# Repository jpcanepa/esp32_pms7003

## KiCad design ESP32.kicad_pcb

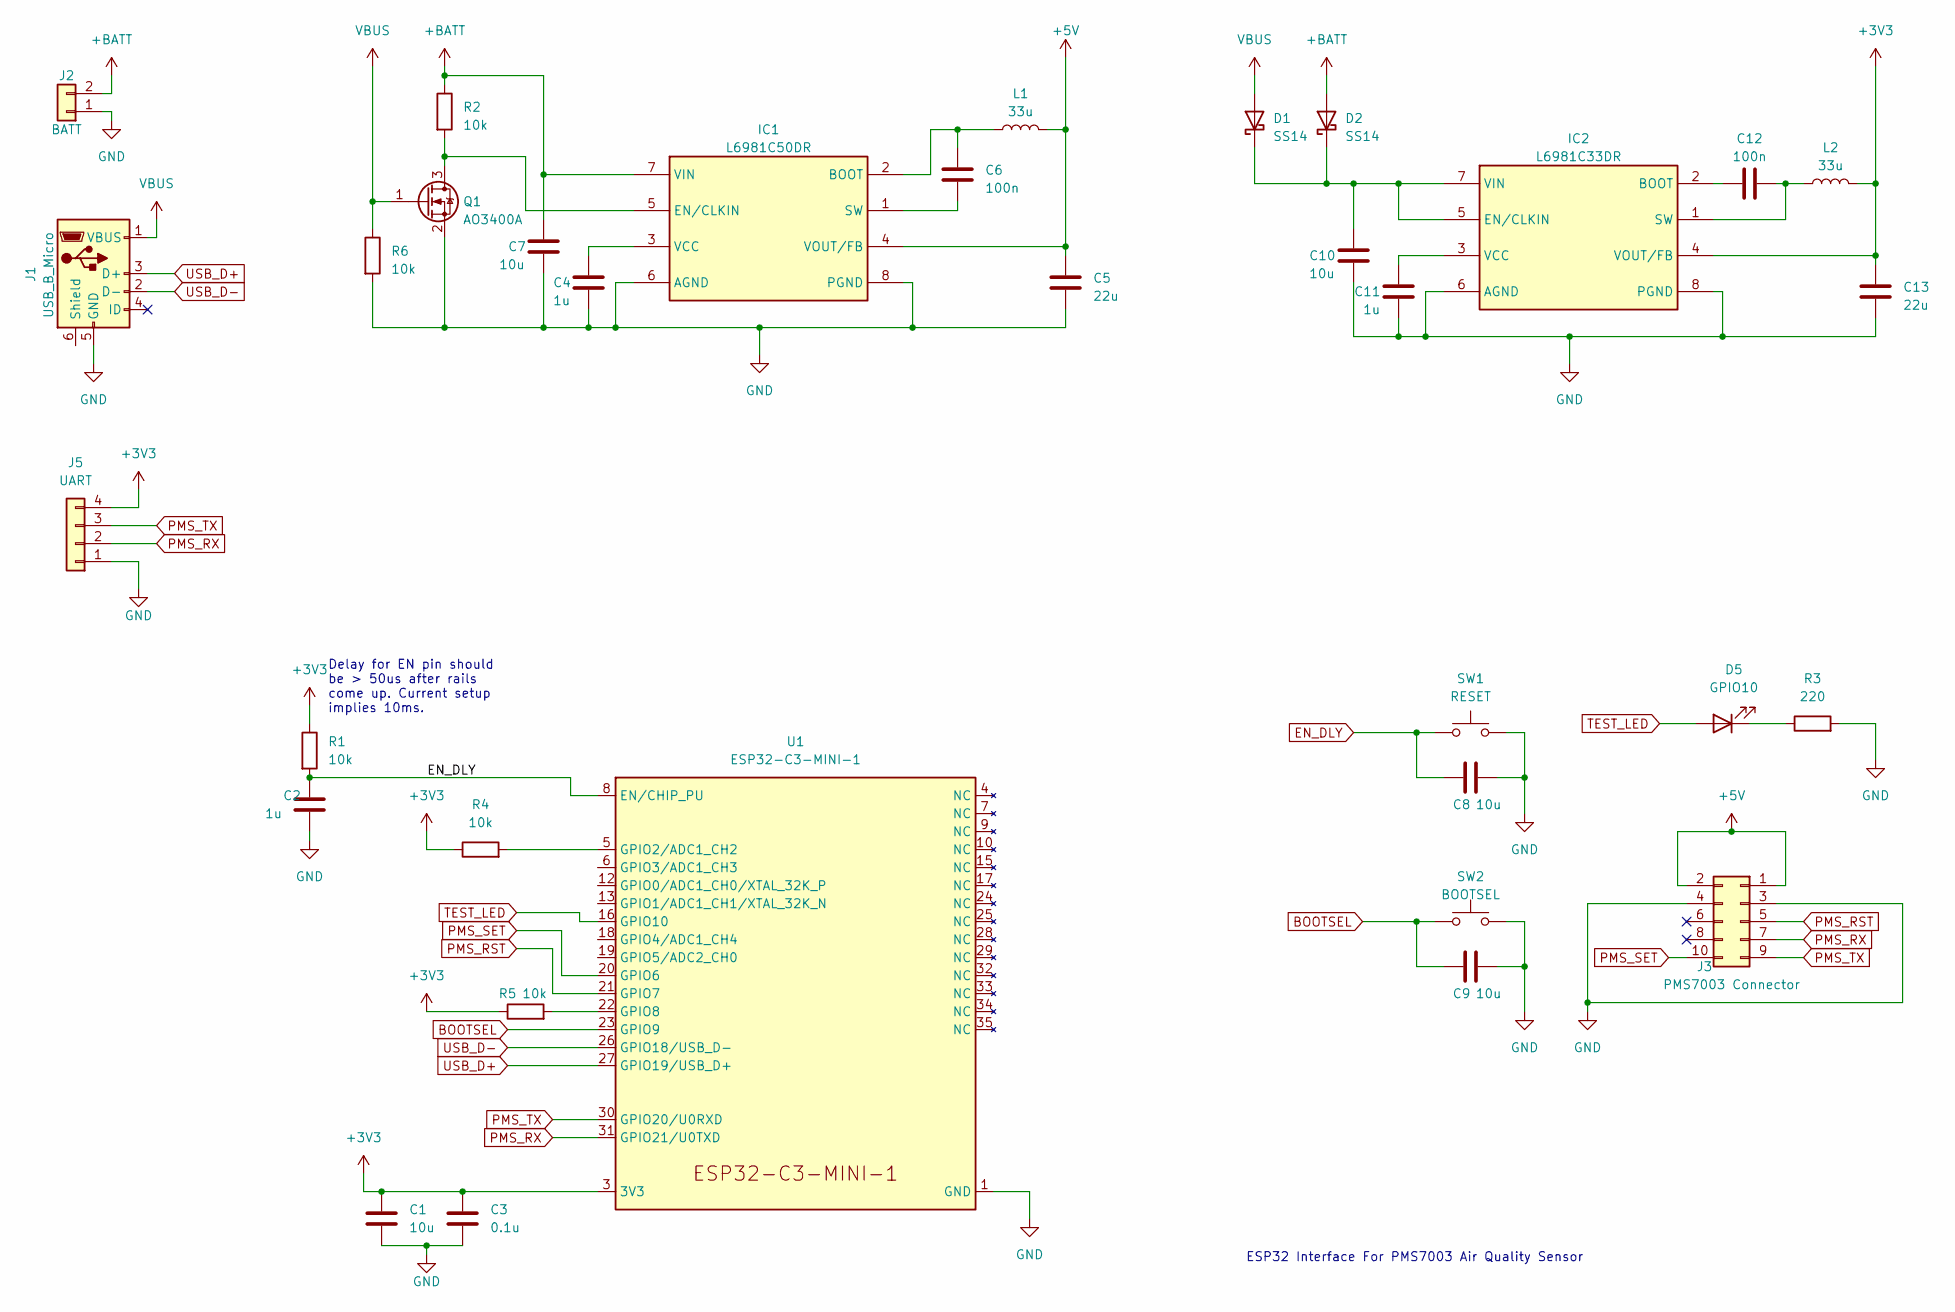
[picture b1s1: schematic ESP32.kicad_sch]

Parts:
C1, C7, C8, C9, C10: 10u; C_0603_1608Metric_Pad1.08x0.95mm_HandSolder
C2, C4, C11: 1u; C_0603_1608Metric_Pad1.08x0.95mm_HandSolder
C3: 0.1u; C_0603_1608Metric_Pad1.08x0.95mm_HandSolder
C5, C13: 22u; C_0603_1608Metric_Pad1.08x0.95mm_HandSolder
C6, C12: 100n; C_0603_1608Metric_Pad1.08x0.95mm_HandSolder
D1, D2: SS14; D_SMA_Handsoldering
D5: GPIO10; LED_0603_1608Metric_Pad1.05x0.95mm_HandSolder
IC1: L6981C50DR; SOIC127P600X175-8N; Mouser Part Number 511-L6981C50DR
IC2: L6981C33DR; SOIC127P600X175-8N; Mouser Part Number 511-L6981C50DR
J1: USB_B_Micro; USB_Mini-B_Wuerth_65100516121_Horizontal
J2: BATT; PinHeader_1x02_P2.54mm_Vertical_SMD_Pin1Right
J3: PMS7003 Connector; PinSocket_2x05_P1.27mm_Vertical_SMD
J5: UART; PinHeader_1x04_P2.54mm_Vertical_SMD_Pin1Right
L1, L2: 33u; L_Murata_29xxxC
Q1: AO3400A; SOT-23
R1, R2, R4, R5, R6: 10k; R_0603_1608Metric_Pad0.98x0.95mm_HandSolder
R3: 220; R_0603_1608Metric_Pad0.98x0.95mm_HandSolder
SW1: RESET; SW_Push_1P1T_NO_Vertical_Wuerth_434133025816
SW2: BOOTSEL; SW_Push_1P1T_NO_Vertical_Wuerth_434133025816
U1: ESP32-C3-MINI-1

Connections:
+3V3: C1.1, C3.1, C13.1, IC2.4 (VOUT/FB), J5.4, L2.2, R1.1, R4.1, R5.1, U1.3 (3V3)
+5V: C5.1, IC1.4 (VOUT/FB), J3.1, J3.2, L1.2
+BATT: C7.1, D2.2 (A), IC1.7 (VIN), J2.2, R2.1
BOOTSEL: C9.1, SW2.1, U1.23 (GPIO9)
EN_DLY: C2.1, C8.1, R1.2, SW1.1, U1.8 (EN/CHIP_PU)
GND: C1.2, C2.2, C3.2, C4.2, C5.2, C7.2, C8.2, C9.2, C10.2, C11.2, C13.2, IC1.6 (AGND), IC1.8 (PGND), IC2.6 (AGND), IC2.8 (PGND), J1.5 (GND), J2.1, J3.3, J3.4, J5.1, Q1.2 (S), R3.2, R6.2, SW1.2, SW2.2, U1.1 (GND), U1.2 (GND), U1.36 (GND), U1.37 (GND), U1.38 (GND), U1.39 (GND), U1.40 (GND), U1.41 (GND), U1.42 (GND), U1.43 (GND), U1.44 (GND), U1.45 (GND), U1.46 (GND), U1.47 (GND), U1.48 (GND), U1.49 (GND), U1.50 (GND), U1.51 (GND), U1.52 (GND), U1.53 (GND)
unnamed: C10.1, D1.1 (K), D2.1 (K), IC2.5 (EN/CLKIN), IC2.7 (VIN)
unnamed: D5.1 (K), R3.1
unnamed: C6.2, IC1.2 (BOOT), L1.1
unnamed: IC1.5 (EN/CLKIN), Q1.3 (D), R2.2
unnamed: C6.1, IC1.1 (SW)
unnamed: C4.1, IC1.3 (VCC)
unnamed: C12.1, IC2.2 (BOOT)
unnamed: C12.2, IC2.1 (SW), L2.1
unnamed: C11.1, IC2.3 (VCC)
unnamed: R4.2, U1.5 (GPIO2/ADC1_CH2)
unnamed: R5.2, U1.22 (GPIO8)
PMS_RST: J3.5, U1.21 (GPIO7)
PMS_RX: J3.7, J5.2, U1.31 (GPIO21/U0TXD)
PMS_SET: J3.10, U1.20 (GPIO6)
PMS_TX: J3.9, J5.3, U1.30 (GPIO20/U0RXD)
TEST_LED: D5.2 (A), U1.16 (GPIO10)
USB_D+: J1.3 (D+), U1.27 (GPIO19/USB_D+)
USB_D-: J1.2 (D-), U1.26 (GPIO18/USB_D-)
VBUS: D1.2 (A), J1.1 (VBUS), Q1.1 (G), R6.1

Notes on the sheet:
Delay for EN pin should be > 50us after rails come up. Current setup implies 10ms.
ESP32 Interface For PMS7003 Air Quality Sensor

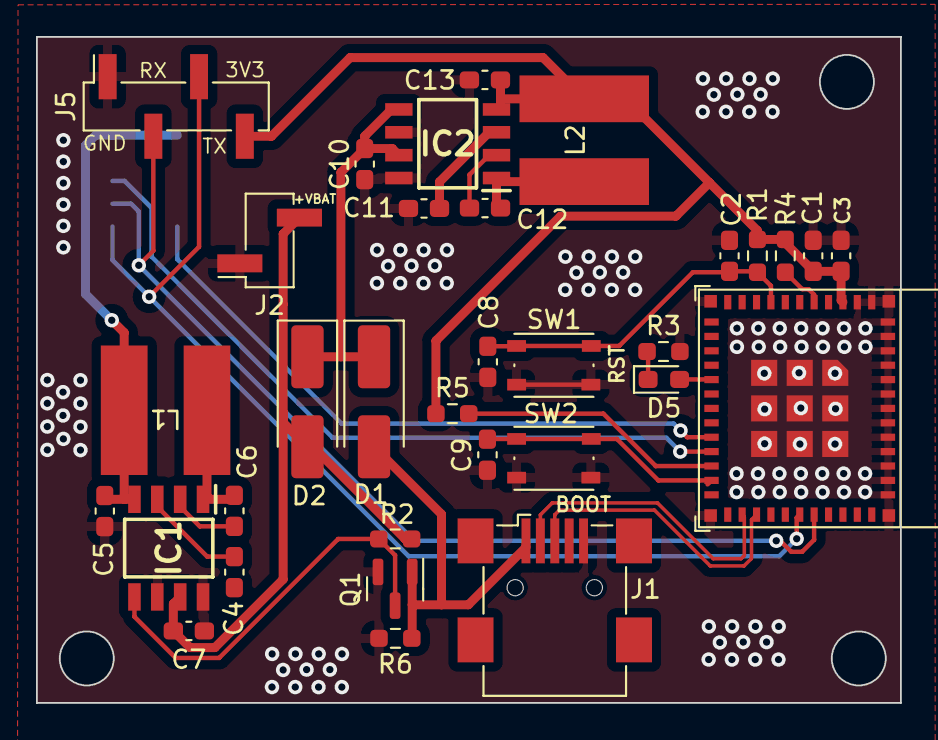
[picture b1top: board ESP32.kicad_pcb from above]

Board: 2 copper layers, 48.0 x 37.0 mm, 34 parts (1 on the bottom side), 25 nets.

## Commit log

2023-03-16 Rework of power + PCB cleanup
2023-03-16 Add gitignore
2023-03-16 New layout routing
2023-03-29 Better power handling
2023-03-29 Updated ignore rules
2023-03-29 Remove deleted files
2023-03-29 Correct placement of the PMS header
2023-04-06 Sch layout + reroute
2023-04-08 Replaced linear regulators with buck converters
2023-04-24 Schematic + Layout
